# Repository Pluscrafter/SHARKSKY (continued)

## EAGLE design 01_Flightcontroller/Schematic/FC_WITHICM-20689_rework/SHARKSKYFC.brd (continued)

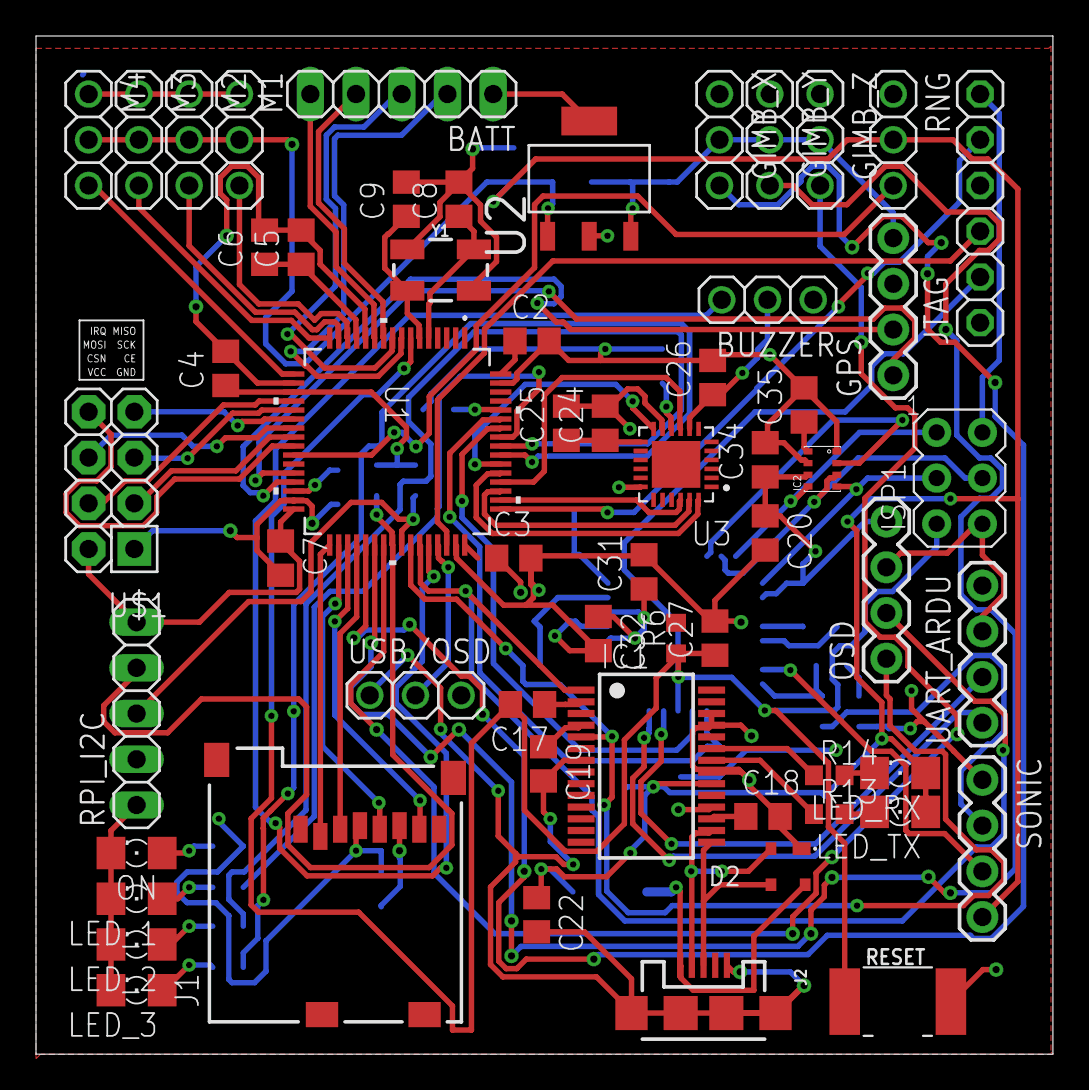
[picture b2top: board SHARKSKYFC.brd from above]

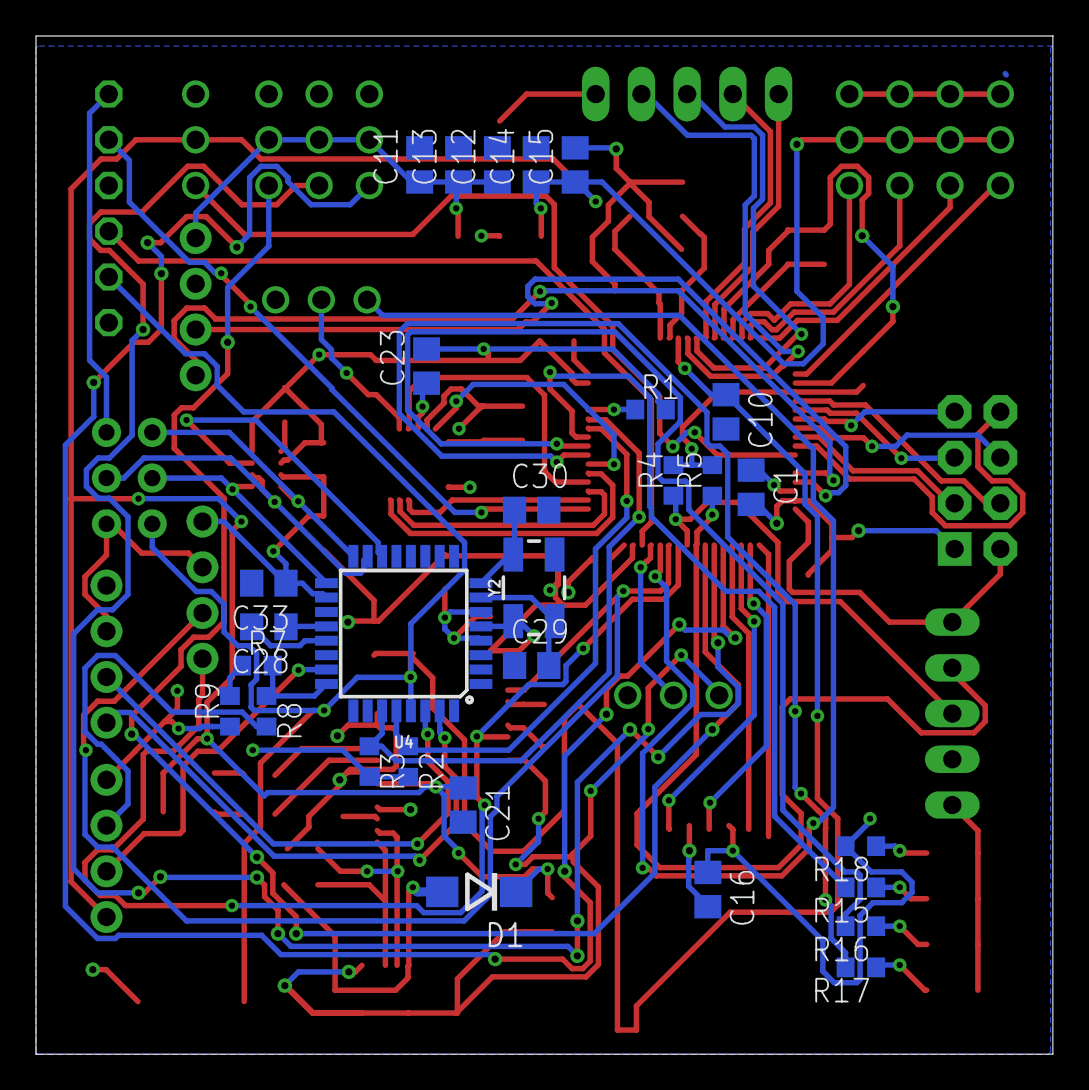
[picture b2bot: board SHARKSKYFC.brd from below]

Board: 2 copper layers, 56.5 x 56.6 mm, 88 parts (29 on the bottom side), 77 nets.

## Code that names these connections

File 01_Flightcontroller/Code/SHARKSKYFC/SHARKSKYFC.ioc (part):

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Mcu.Name=STM32F722R(C-E)Tx
Mcu.Package=LQFP64
Mcu.UserName=STM32F722RETx
PA0-WKUP.Signal=S_TIM2_CH1_ETR
PA1.Signal=S_TIM2_CH2
PA10.GPIOParameters=GPIO_Label
PA10.GPIO_Label=USBOSD_RX
PA10.Mode=Asynchronous
PA10.Signal=USART1_RX
PA11.GPIOParameters=GPIO_Label
PA11.GPIO_Label=BUZZER
PA11.Signal=GPIO_Output
PA12.GPIOParameters=GPIO_Label
PA12.GPIO_Label=USBOSD
PA12.Signal=GPIO_Input
PA13.Mode=Serial_Wire
PA13.Signal=SYS_JTMS-SWDIO
PA14.Mode=Serial_Wire
PA14.Signal=SYS_JTCK-SWCLK
PA15.GPIOParameters=GPIO_Label
PA15.GPIO_Label=IMU_NSS
PA15.Mode=NSS_Signal_Hard_Output
PA15.Signal=SPI3_NSS
PA2.Signal=S_TIM2_CH3
PA3.Signal=S_TIM2_CH4
PA4.GPIOParameters=GPIO_Label
PA4.GPIO_Label=RF24_NSS
PA4.Mode=NSS_Signal_Hard_Output
PA4.Signal=SPI1_NSS
PA5.GPIOParameters=GPIO_Label
PA5.GPIO_Label=RF24_SCK
PA5.Mode=Full_Duplex_Master
PA5.Signal=SPI1_SCK
PA6.GPIOParameters=GPIO_Label
PA6.GPIO_Label=RF24_MISO
PA6.Mode=Full_Duplex_Master
PA6.Signal=SPI1_MISO
PA7.GPIOParameters=GPIO_Label
PA7.GPIO_Label=RF24_MOSI
PA7.Mode=Full_Duplex_Master
PA7.Signal=SPI1_MOSI
PA8.GPIOParameters=GPIO_Label
PA8.GPIO_Label=RPI_SCL
PA8.Mode=I2C
PA8.Signal=I2C3_SCL
PA9.GPIOParameters=GPIO_Label
PA9.GPIO_Label=UBSOSD_TX
PA9.Mode=Asynchronous
PA9.Signal=USART1_TX
PB0.GPIOParameters=GPIO_Label
PB0.GPIO_Label=RF24_INT
PB0.Signal=GPXTI0
PB1.GPIOParameters=GPIO_Label
PB1.GPIO_Label=RNG_ADC
PB1.Signal=ADCx_IN9
PB10.GPIOParameters=GPIO_Label
PB10.GPIO_Label=GPS_TX
PB10.Mode=Asynchronous
PB10.Signal=USART3_TX
PB11.GPIOParameters=GPIO_Label
PB11.GPIO_Label=GPS_RX
PB11.Mode=Asynchronous
PB11.Signal=USART3_RX
PB12.GPIOParameters=GPIO_Label
PB12.GPIO_Label=SD_NSS
PB12.Mode=NSS_Signal_Hard_Output
PB12.Signal=SPI2_NSS
PB13.GPIOParameters=GPIO_Label
PB13.GPIO_Label=SD_SCK
PB13.Mode=Full_Duplex_Master
PB13.Signal=SPI2_SCK
PB14.GPIOParameters=GPIO_Label
PB14.GPIO_Label=SD_MISO
PB14.Mode=Full_Duplex_Master
PB14.Signal=SPI2_MISO
PB15.GPIOParameters=GPIO_Label
PB15.GPIO_Label=SD_MOSI
PB15.Mode=Full_Duplex_Master
PB15.Signal=SPI2_MOSI
PB3.GPIOParameters=GPIO_Label
PB3.GPIO_Label=LED_3
PB3.Signal=GPIO_Output
PB4.GPIOParameters=GPIO_Label
PB4.GPIO_Label=LED_2
PB4.Signal=GPIO_Output
PB5.GPIOParameters=GPIO_Label
PB5.GPIO_Label=LED_1
PB5.Signal=GPIO_Output
PB6.GPIOParameters=GPIO_Label
PB6.GPIO_Label=ARDU_SCL
PB6.Mode=I2C
PB6.Signal=I2C1_SCL
PB7.GPIOParameters=GPIO_Label
PB7.GPIO_Label=ARDU_SDA
PB7.Mode=I2C
PB7.Signal=I2C1_SDA
PB8.GPIOParameters=GPIO_Label
PB8.GPIO_Label=LLVOE
PB8.Signal=GPIO_Output
PC0.GPIOParameters=GPIO_Label
PC0.GPIO_Label=CELL_4
PC0.Signal=ADCx_IN10
PC1.GPIOParameters=GPIO_Label
PC1.GPIO_Label=CELL_3
PC1.Signal=ADCx_IN11
PC10.GPIOParameters=GPIO_Label
PC10.GPIO_Label=IMU_SCK
PC10.Mode=Full_Duplex_Master
PC10.Signal=SPI3_SCK
PC11.GPIOParameters=GPIO_Label
PC11.GPIO_Label=IMU_MISO
PC11.Mode=Full_Duplex_Master
PC11.Signal=SPI3_MISO
PC12.GPIOParameters=GPIO_Label
PC12.GPIO_Label=IMU_MOSI
PC12.Mode=Full_Duplex_Master
PC12.Signal=SPI3_MOSI
PC2.GPIOParameters=GPIO_Label
PC2.GPIO_Label=CELL_2
PC2.Signal=ADCx_IN12
PC3.GPIOParameters=GPIO_Label
PC3.GPIO_Label=CELL_1
PC3.Signal=ADCx_IN13
PC4.GPIOParameters=GPIO_Label
PC4.GPIO_Label=RF24_CE
PC4.Signal=GPIO_Output
PC6.Signal=S_TIM3_CH1
PC7.Signal=S_TIM3_CH2
PC8.Signal=S_TIM3_CH3
PC9.GPIOParameters=GPIO_Label
PC9.GPIO_Label=RPI_SDA
PC9.Mode=I2C
PC9.Signal=I2C3_SDA
PD2.GPIOParameters=GPIO_Label
PD2.GPIO_Label=IMU_INT
PD2.Signal=GPXTI2
PH0-OSC_IN.Mode=HSE-External-Oscillator
PH0-OSC_IN.Signal=RCC_OSC_IN
PH1-OSC_OUT.Mode=HSE-External-Oscillator
PH1-OSC_OUT.Signal=RCC_OSC_OUT
RCC.HSE_VALUE=8000000
RCC.SYSCLKFreq_VALUE=216000000
RCC.SYSCLKSource=RCC_SYSCLKSOURCE_PLLCLK
board=custom

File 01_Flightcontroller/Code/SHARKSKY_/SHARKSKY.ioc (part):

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Mcu.Name=STM32F722R(C-E)Tx
Mcu.Package=LQFP64
Mcu.UserName=STM32F722RETx
PA0-WKUP.GPIOParameters=GPIO_Label
PA0-WKUP.GPIO_Label=MOTOR_1
PA0-WKUP.Signal=S_TIM2_CH1_ETR
PA1.GPIOParameters=GPIO_Label
PA1.GPIO_Label=MOTOR_2
PA1.Signal=S_TIM2_CH2
PA10.GPIOParameters=GPIO_Label
PA10.GPIO_Label=FTDI_RX
PA10.Mode=Asynchronous
PA10.Signal=USART1_RX
PA11.GPIOParameters=GPIO_Label
PA11.GPIO_Label=LLVOE
PA11.Signal=GPIO_Output
PA12.GPIOParameters=GPIO_PuPd,GPIO_Label
PA12.GPIO_Label=USBOSD
PA12.GPIO_PuPd=GPIO_NOPULL
PA12.Signal=GPIO_Input
PA13.Mode=Serial_Wire
PA13.Signal=SYS_JTMS-SWDIO
PA14.Mode=Serial_Wire
PA14.Signal=SYS_JTCK-SWCLK
PA2.GPIOParameters=GPIO_Label
PA2.GPIO_Label=GPS_TX
PA2.Mode=Asynchronous
PA2.Signal=USART2_TX
PA3.GPIOParameters=GPIO_Label
PA3.GPIO_Label=GPS_RX
PA3.Mode=Asynchronous
PA3.Signal=USART2_RX
PA4.GPIOParameters=GPIO_Speed,PinState,GPIO_Label
PA4.GPIO_Label=IMU_NSS
PA4.GPIO_Speed=GPIO_SPEED_FREQ_VERY_HIGH
PA4.PinState=GPIO_PIN_SET
PA4.Signal=GPIO_Output
PA5.Signal=COMP_DAC2_group
PA6.Signal=ADCx_IN6
PA7.GPIOParameters=GPIO_Label
PA7.GPIO_Label=INIT_OK
PA7.Signal=GPIO_Output
PA8.GPIOParameters=GPIO_Label
PA8.GPIO_Label=ARDU_SCL
PA8.Mode=I2C
PA8.Signal=I2C3_SCL
PA9.GPIOParameters=GPIO_Label
PA9.GPIO_Label=FTDI_TX
PA9.Mode=Asynchronous
PA9.Signal=USART1_TX
PB0.GPIOParameters=GPIO_Label
PB0.GPIO_Label=GIMBAL_X
PB0.Signal=S_TIM3_CH3
PB1.GPIOParameters=GPIO_Label
PB1.GPIO_Label=MOD1_LED
PB1.Signal=GPIO_Output
PB10.GPIOParameters=GPIO_Label
PB10.GPIO_Label=MOTOR_3
PB10.Signal=S_TIM2_CH3
PB11.GPIOParameters=GPIO_Label
PB11.GPIO_Label=MOTOR_4
PB11.Signal=S_TIM2_CH4
PB12.GPIOParameters=GPIO_Speed,PinState,GPIO_PuPd,GPIO_Label
PB12.GPIO_Label=RF24_NSS
PB12.GPIO_PuPd=GPIO_PULLUP
PB12.GPIO_Speed=GPIO_SPEED_FREQ_VERY_HIGH
PB12.PinState=GPIO_PIN_SET
PB12.Signal=GPIO_Output
PB13.GPIOParameters=GPIO_Label
PB13.GPIO_Label=RF24_SCK
PB13.Mode=Full_Duplex_Master
PB13.Signal=SPI2_SCK
PB2.GPIOParameters=GPIO_Label
PB2.GPIO_Label=IMU_MOSI
PB2.Mode=Full_Duplex_Master
PB2.Signal=SPI3_MOSI
PB4.GPIOParameters=GPIO_Label
PB4.GPIO_Label=GIMBAL_Y
PB4.Signal=S_TIM3_CH1
PB5.GPIOParameters=GPIO_Label
PB5.GPIO_Label=GIMBAL_Z
PB5.Signal=S_TIM3_CH2
PB6.GPIOParameters=GPIO_Label
PB6.GPIO_Label=IMU2_SCL
PB6.Mode=I2C
PB6.Signal=I2C1_SCL
PB7.GPIOParameters=GPIO_Label
PB7.GPIO_Label=IMU2_SDA
PB7.Mode=I2C
PB7.Signal=I2C1_SDA
PB8.GPIOParameters=GPIO_Label
PB8.GPIO_Label=INTA
PB8.Signal=GPXTI8
PB9.GPIOParameters=GPIO_Label
PB9.GPIO_Label=IMU_INT
PB9.Signal=GPXTI9
PC1.GPIOParameters=GPIO_Label
PC1.GPIO_Label=RF24_MOSI
PC1.Mode=Full_Duplex_Master
PC1.Signal=SPI2_MOSI
PC10.GPIOParameters=GPIO_Label
PC10.GPIO_Label=IMU_SCK
PC10.Mode=Full_Duplex_Master
PC10.Signal=SPI3_SCK
PC11.GPIOParameters=GPIO_Label
PC11.GPIO_Label=IMU_MISO
PC11.Mode=Full_Duplex_Master
PC11.Signal=SPI3_MISO
PC12.Mode=SD_1_bit
PC12.Signal=SDMMC1_CK
PC2.GPIOParameters=GPIO_Label
PC2.GPIO_Label=RF24_MISO
PC2.Mode=Full_Duplex_Master
PC2.Signal=SPI2_MISO
PC4.GPIOParameters=GPIO_Label
PC4.GPIO_Label=MOD0_LED
PC4.Signal=GPIO_Output
PC6.GPIOParameters=GPIO_Label
PC6.GPIO_Label=CE
PC6.Signal=GPIO_Output
PC7.GPIOParameters=GPIO_Label
PC7.GPIO_Label=IRQ
PC7.Signal=GPXTI7
PC8.Mode=SD_1_bit
PC8.Signal=SDMMC1_D0
PC9.GPIOParameters=GPIO_Label
PC9.GPIO_Label=ARDU_SDA
PC9.Mode=I2C
PC9.Signal=I2C3_SDA
PD2.Mode=SD_1_bit
PD2.Signal=SDMMC1_CMD
PH0-OSC_IN.Mode=HSE-External-Oscillator
PH0-OSC_IN.Signal=RCC_OSC_IN
PH1-OSC_OUT.Mode=HSE-External-Oscillator
PH1-OSC_OUT.Signal=RCC_OSC_OUT
RCC.HSE_VALUE=8000000
RCC.SYSCLKFreq_VALUE=216000000
RCC.SYSCLKSource=RCC_SYSCLKSOURCE_PLLCLK
board=custom

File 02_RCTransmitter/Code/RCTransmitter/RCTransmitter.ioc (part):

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Mcu.Name=STM32F767ZITx
Mcu.Package=LQFP144
Mcu.UserName=STM32F767ZITx
PA1.Mode=RMII
PA1.Signal=ETH_REF_CLK
PA10.GPIOParameters=GPIO_Label
PA10.GPIO_Label=USB_ID
PA10.Signal=USB_OTG_FS_ID
PA11.GPIOParameters=GPIO_Label
PA11.GPIO_Label=USB_DM
PA11.Mode=Device_Only
PA11.Signal=USB_OTG_FS_DM
PA12.GPIOParameters=GPIO_Label
PA12.GPIO_Label=USB_DP
PA12.Mode=Device_Only
PA12.Signal=USB_OTG_FS_DP
PA13.GPIOParameters=GPIO_Label
PA13.GPIO_Label=TMS
PA13.Mode=Serial_Wire
PA13.Signal=SYS_JTMS-SWDIO
PA14.GPIOParameters=GPIO_Label
PA14.GPIO_Label=TCK
PA14.Mode=Serial_Wire
PA14.Signal=SYS_JTCK-SWCLK
PA2.Mode=RMII
PA2.Signal=ETH_MDIO
PA3.Signal=ADCx_IN3
PA4.Mode=NSS_Signal_Hard_Output
PA4.Signal=SPI1_NSS
PA5.Mode=Full_Duplex_Master
PA5.Signal=SPI1_SCK
PA7.Mode=RMII
PA7.Signal=ETH_CRS_DV
PA8.GPIOParameters=GPIO_Label
PA8.GPIO_Label=USB_SOF [TP1]
PA8.Mode=Activate_SOF_FS
PA8.Signal=USB_OTG_FS_SOF
PA9.GPIOParameters=GPIO_Label
PA9.GPIO_Label=USB_VBUS
PA9.Mode=Activate_VBUS
PA9.Signal=USB_OTG_FS_VBUS
PB13.Mode=RMII
PB13.Signal=ETH_TXD1
PB14.GPIOParameters=GPIO_Label
PB14.GPIO_Label=LD3 [Red]
PB14.Signal=GPIO_Output
PB3.GPIOParameters=GPIO_Label
PB3.GPIO_Label=SWO
PB3.Signal=SYS_JTDO-SWO
PB4.Mode=Full_Duplex_Master
PB4.Signal=SPI1_MISO
PB5.Mode=Full_Duplex_Master
PB5.Signal=SPI1_MOSI
PB7.GPIOParameters=GPIO_Label
PB7.GPIO_Label=LD2 [Blue]
PB7.Signal=GPIO_Output
PB8.Mode=I2C
PB8.Signal=I2C1_SCL
PB9.Mode=I2C
PB9.Signal=I2C1_SDA
PC0.Signal=ADCx_IN10
PC1.Mode=RMII
PC1.Signal=ETH_MDC
PC12.Mode=SD_1_bit
PC12.Signal=SDMMC1_CK
PC13.GPIOParameters=GPIO_Label
PC13.GPIO_Label=USER_Btn [B1]
PC13.Signal=GPXTI13
PC14/OSC32_IN.Mode=LSE-External-Oscillator
PC14/OSC32_IN.Signal=RCC_OSC32_IN
PC15/OSC32_OUT.Mode=LSE-External-Oscillator
PC15/OSC32_OUT.Signal=RCC_OSC32_OUT
PC3.Signal=ADCx_IN13
PC4.Mode=RMII
PC4.Signal=ETH_RXD0
PC5.Mode=RMII
PC5.Signal=ETH_RXD1
PC8.Mode=SD_1_bit
PC8.Signal=SDMMC1_D0
PD14.Signal=GPIO_Output
PD15.Signal=GPIO_Output
PD2.Mode=SD_1_bit
PD2.Signal=SDMMC1_CMD
PD8.GPIOParameters=GPIO_Label
PD8.GPIO_Label=STLK_RX [STM32F103CBT6_PA3]
PD8.Mode=Asynchronous
PD8.Signal=USART3_TX
PD9.GPIOParameters=GPIO_Label
PD9.GPIO_Label=STLK_TX [STM32F103CBT6_PA2]
PD9.Mode=Asynchronous
PD9.Signal=USART3_RX
PE11.GPIOParameters=GPIO_PuPd,GPIO_Label
PE11.GPIO_Label=SW3
PE11.GPIO_PuPd=GPIO_PULLUP
PE11.Signal=GPIO_Input
PE13.GPIOParameters=GPIO_PuPd,GPIO_Label
PE13.GPIO_Label=BTN_R
PE13.GPIO_PuPd=GPIO_PULLUP
PE13.Signal=GPIO_Input
PE9.GPIOParameters=GPIO_PuPd,GPIO_Label
PE9.GPIO_Label=SW2
PE9.GPIO_PuPd=GPIO_PULLUP
PE9.Signal=GPIO_Input
PF0.Signal=I2C2_SDA
PF1.Signal=I2C2_SCL
PF10.Mode=IN8
PF10.Signal=ADC3_IN8
PF13.GPIOParameters=GPIO_PuPd,GPIO_Label
PF13.GPIO_Label=SW1
PF13.GPIO_PuPd=GPIO_PULLUP
PF13.Signal=GPIO_Input
PF14.GPIOParameters=GPIO_PuPd,GPIO_Label
PF14.GPIO_Label=SW4
PF14.GPIO_PuPd=GPIO_PULLUP
PF14.Signal=GPIO_Input
PF15.GPIOParameters=GPIO_PuPd,GPIO_Label
PF15.GPIO_Label=BTN_D
PF15.GPIO_PuPd=GPIO_PULLUP
PF15.Signal=GPIO_Input
PF3.Mode=IN9
PF3.Signal=ADC3_IN9
PF5.Mode=IN15
PF5.Signal=ADC3_IN15
PF8.GPIOParameters=GPIO_PuPd,GPIO_Label
PF8.GPIO_Label=BTN_L
PF8.GPIO_PuPd=GPIO_PULLUP
PF8.Signal=GPIO_Input
PG11.Mode=RMII
PG11.Signal=ETH_TX_EN
PG13.Mode=RMII
PG13.Signal=ETH_TXD0
PG14.GPIOParameters=GPIO_PuPd,GPIO_Label
PG14.GPIO_Label=BTN_M
PG14.GPIO_PuPd=GPIO_PULLUP
PG14.Signal=GPIO_Input
PG6.GPIOParameters=GPIO_Label
PG6.GPIO_Label=USB_PowerSwitchOn [STMPS2151STR_EN]
PG6.Signal=GPIO_Output
PG7.GPIOParameters=GPIO_Label
PG7.GPIO_Label=USB_OverCurrent [STMPS2151STR_FAULT]
PG7.Signal=GPIO_Input
PG9.GPIOParameters=GPIO_PuPd,GPIO_Label
PG9.GPIO_Label=BTN_U
PG9.GPIO_PuPd=GPIO_PULLUP
PG9.Signal=GPIO_Input
PH0/OSC_IN.GPIOParameters=GPIO_Label
PH0/OSC_IN.GPIO_Label=MCO [STM32F103CBT6_PA8]
PH0/OSC_IN.Mode=HSE-External-Clock-Source
PH0/OSC_IN.Signal=RCC_OSC_IN
PH1/OSC_OUT.Mode=HSE-External-Clock-Source
PH1/OSC_OUT.Signal=RCC_OSC_OUT
RCC.HSE_VALUE=8000000
RCC.SYSCLKFreq_VALUE=216000000
RCC.SYSCLKSource=RCC_SYSCLKSOURCE_PLLCLK
RCC.SYSCLKSourceVirtual=RCC_SYSCLKSOURCE_PLLCLK
board=NUCLEO-F767ZI
boardIOC=true

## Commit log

2019-03-21 Erstellen von Arbeitsordnern Suchen der möglich brauchbaren Datenblätter Suchen der Bauteile
2019-03-21 Einfügen von README
2019-03-22 Hinzufügen des LDO-VR und dessen Filter Caps
2019-03-24 Einfügen von mehr Teilen in Partslist.txt Anfangen des Leiterplattendisigns. Anfangen des schriftlichen Teil. Anfangen Pin Assigment Microcontroller für das programmieren.
2019-03-25 Ändern des Titels
2019-03-28 Hinzufügen des BMP280 -> ändern auf 3V3 LOGIK mit Chip oder Mosfet
2019-03-29 Hinzufügen LogicLevelShifter
2019-03-31 -Schaltung hinzufügen von Pins und Wiederständen -Schriftlicher Teil Hinzfügen von Bauteil des Flightconrollers.
2019-04-01 Schelmischer Versuch von Board Design 215 Vias :)
2019-04-02 -delete Word
2019-04-02 Hinzufügen STNUCLEO144_MANUAL.pdf
2019-04-03 JTAG -> Serial Wire
2019-04-05 Löschen von ünnötigen Pins
2019-04-08 Versuchen vom routen 143Vias -> 143 Sorgetelefon :).
2019-04-10 Richtiges routen hilfe durch bruno
2019-04-10 Hinzufügen USB , BATTSENS und VCC/GNDLAYER
2019-04-12 Finnishing Board up. BOM
2019-04-14 Fertig machen Besprechung mit Bruno Bestellungsliste 2FC's mit MPU und ICM
2019-04-15 Umdrehen SD Karte
2019-04-16 Daten Für Bestellungen
2019-04-25 SPI funzt
2019-04-25 SPI WORKS! maybe ...
2019-04-30 SPI datenlesen MPU6500;
2019-05-19 Neu Board fertig Testprogramm FTDI OK PWM OK LED OK
2019-05-24 add pic PWM
2019-05-25 Add dma
2019-05-29 -Add initalizing Code -rename pdf's
2019-05-31 read IMU ok
2019-06-01 resolve print float -> Linker problem -> bug in CUBEMX gyro to stable
2019-06-02 Working read ACCEL and GYRO
2019-06-07 Offset finding WIP
2019-06-07 -OFFSET WIP -Temperature WIP -Abstraktion der Abstraktion ok
2019-06-09 - Offset OK - I_SPI WriteRegisters BUG
2019-06-09 -ICM20689 realANGLE works but overshooting -ADD MPU6050 with DMP
2019-06-10 -rename MPU6050_.h and MPU6050_.cpp namespace from 'Sensors' to 'Sensor' to match ICM20689 class -first tryings with Doxygen -> CSS style form SFML Simple and Fast Multimedia Library
2019-06-13 Add NRF24 Doc unsucessful test of rf24
2019-06-14 -Add complementary filter disable RF24
2019-06-14 other nrf24 lib
2019-07-03 add NRF24 lib with DMA -> test and debug other libs fail.
2019-07-03 add pictures soldering and SPI fail and success
2019-07-20 no DMA for nRF -> other time...
2019-07-20 ADD eclipse IDE files to ignore list
    ADD eclipse IDE files to ignore list for obvious reasons.
2019-07-20 rename 04_Schriftliche Arbeit
2019-07-21 update gitattributes
2019-07-21 add Frontpanel of Transmitter
2019-07-22 add Test Frontpanel
2019-07-23 finish build transmitter
2019-07-23 update Front and back
2019-07-23 add dxf
2019-07-23 add rd files for laser
2019-08-06 add PID and update Doc
2019-08-06 Update Doxyfile
2019-08-07 add RCTransmitter code
2019-08-28 rf24 dma
2019-09-19 add LCD-Driver
    https://github.com/firebull/STM32-LCD-HD44780-I2C
2019-09-19 Millimeterarbeit für schalter
2019-09-19 move RCTransmitter to right folder
2019-09-19 add NRF24-lib to RCTransmitter
2019-09-22 add not added nrf24l01.h TODO LCD without RTOS
2019-09-22 change errors in Text according to teacher
2019-09-24 testfähig
    RCTransmitter
    add lcd_hd11480 rtos -> class
    add ADC dma
    add NRF24
    add sender struct
    add radioloop
2019-09-25 First Tests
    - Roll false correction
    TODO correct Roll
    TODO Pitch Roll sync with transmitter
    TODO yaw -> anglemotion
2019-09-25 corrected roll correction
    corrected roll correction
2019-09-29 NRF24 remove HAL_GPIO_WRITE -> registering
2019-09-29 change clk to 200Mhz better division
2019-09-29 add media
2019-09-29 parent d01b85a6160d2375ebbbcc1e4aa164b7856fb4d3 author Pluscrafter <pluscrafter123@hotmail.com> 1563666210 +0200 committer Pluscrafter <pluscrafter123@hotmail.com> 1569777323 +0200
    Create .gitattributes
    Update .gitattributes
    Update .gitattributes
    update
    rename 04_Schriftliche Arbeit
    update gitattributes
2019-09-29 remove ST32F722ZE-Board no need to test anymore
2019-09-29 add Websites for Neaples
2019-09-30 remove unecessary pictures
2019-09-30 Verbesserungen Text
2019-10-04 add filter header
2019-10-09 add FilterSim
2019-10-09 add Yaw PID faster loop(40%)
2019-10-09 test with 133hz
2019-10-09 add Digital low-pass
2019-10-10 schreiben bei Schriftlichen
    Einleitung, Was ist ein Quadrocopter?, PID-Regler und Filter
2019-10-10 rem misc ->lager vorbei :-1: , mehr Text
2019-10-10 mehr Text
2019-10-10 add Motorcalib -> to be tested
2019-10-11 SD card working
2019-10-11 SPIBUG
2019-10-11 add SDLogging
2019-10-12 add looptime without in dbg mode
2019-10-12 add FFT and filtersim for quad old filtersim -> filtertester
2019-10-14 update Documentation and comment code
2019-10-15 mehr schriftliches
2019-10-16 Test in school
2019-10-16 add zeroing
2019-10-17 add vid, right pid
2019-10-17 new calibration, other reading sensitivity, add rotationmatrix
2019-10-18 right filter, new logs
2019-10-19 add uart menu
2019-10-20 add gps test
2019-10-26 redesigning FC
2019-10-26 new SCHEMATIC
2019-10-26 update sharkskyfc
2019-10-27 wiring new board
2019-10-27 route new brd
2019-10-27 new pinout
2019-10-27 new pid
2019-10-28 more wiring 9 airwire left
2019-10-28 more text
2019-10-29 add back MPU6500
2019-10-29 read sensors with interrupt
    make sdcard selectable
2019-10-29 remove fix throttle
    loop with 2.5khz
2019-10-31 new PID, corrected Intergal calculation
2019-10-31 add pid read from RCtrans
2019-10-31 rechtschreibefehler
2019-11-04 SOFTWARE NSS
2019-11-04 IMU dma, TODO NRF24 DMA and IRQ
2019-11-08 add differential sending
2019-11-12 Auto stash before merge of "master" and "origin/master"
2019-11-15 new pic
2019-11-19 tim based interrupt
2019-11-20 text title
2019-11-26 more text and pictures
2019-11-26 more Text mor Pics
2019-11-26 only without title pic
2019-11-26 last pic
2019-11-26 update text
2019-11-26 add -
2019-11-28 finishing text
2019-11-28 corrections
2019-11-28 more corrections
2019-11-28 preparing for printing
2019-11-28 Abgabe
2019-11-29 ma without pics
2019-12-12 add angle cutoff and nan correction
2019-12-16 not filtered PID
2019-12-16 better code
2019-12-17 update
    -add defines for dlpf freq, cutoff angle and max correction
    -Max correction 400->600
    -disable dlpf for pitch and roll
    -cutoff angle 25 -> 40
2019-12-17 add zero point correction
2019-12-18 add VIDS and PICS
2019-12-18 Create LICENSE
2019-12-18 revert merge
2019-12-19 Add avg zeropoint on startup 100 pts
2019-12-22 add FC V2
2019-12-22 code cosmetics
2019-12-22 optimization to fast
2019-12-24 add IMU Radio add all function exept reading IMU and radio
2020-01-04 add IMU and fastmath
2020-01-04 add "Cmode" using C style minmal class usage only in init stage
2020-01-04 add forgotten project files for V2
2020-01-06 test on laptop
2020-01-06 add pid sim
2020-01-06 add slider
2020-01-07 projectfiles gitignore ideaIDE
2020-01-09 add arduino BMP280
2020-01-09 set imu to 1khz
2020-01-09 Timer for arduino
2020-01-13 pid sim description
2020-01-16 IMU to loop
2020-01-22 add presentation
2020-01-23 add pid arduino sim
2020-01-23 good pid values
2020-01-26 update praesentation
2020-01-27 add more pics
2020-01-28 add changable pid and angle
2020-01-29 corr präsi
2020-01-29 com ardu python
2020-01-30 false d calc
2020-01-30 better präsi
2020-01-30 change to old
2020-02-14 update V2 to new STMIDE version
2020-02-15 update V1 and remove old fatfs headers
2020-02-15 update arduino code
2020-08-30 new version in C
2020-09-06 DEBUG code
    full dma with interrupt
    TODO first read of GYRO may be inf
2020-10-26 icm angle pitch roll rotation
    nrf32 library import
    TODO dma impl. nrf24
2020-12-03 update ide
2020-12-17 fast loop TCM and ICache
2024-03-04 update and add bare metal impl.
2024-03-05 add timer interrupts
2024-03-22 add PID motor and receiver
